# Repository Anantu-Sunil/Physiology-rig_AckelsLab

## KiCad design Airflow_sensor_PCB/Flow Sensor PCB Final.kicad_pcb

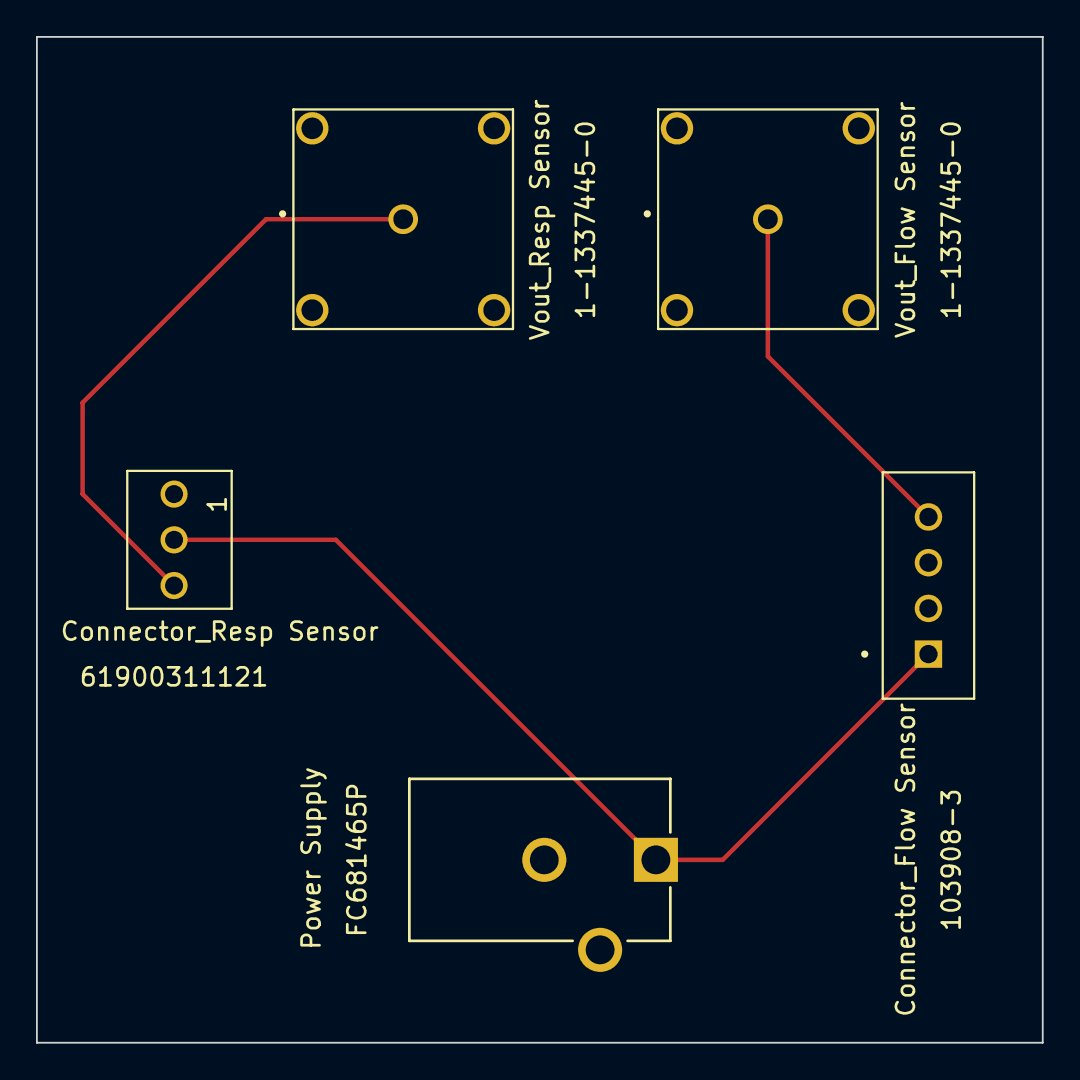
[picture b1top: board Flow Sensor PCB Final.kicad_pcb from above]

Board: 2 copper layers, 55.9 x 55.9 mm, 5 parts (0 on the bottom side), 4 nets.

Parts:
Connector_Flow Sensor: 103908-3; TE_103908-3
Connector_Resp Sensor: 61900311121
Power Supply: FC681465P; CLIFF-FC681465P-0
Vout_Flow Sensor: 1-1337445-0; TE_1-1337445-0
Vout_Resp Sensor: 1-1337445-0; TE_1-1337445-0

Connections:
unnamed: Connector_Flow Sensor.1, Connector_Resp Sensor.2, Power Supply.1
unnamed: Connector_Flow Sensor.2, Connector_Resp Sensor.1, Power Supply.2, Vout_Flow Sensor.2, Vout_Flow Sensor.3, Vout_Flow Sensor.4, Vout_Flow Sensor.5, Vout_Resp Sensor.2, Vout_Resp Sensor.3, Vout_Resp Sensor.4, Vout_Resp Sensor.5
unnamed: Connector_Flow Sensor.4, Vout_Flow Sensor.1
unnamed: Connector_Resp Sensor.3, Vout_Resp Sensor.1

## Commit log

2024-05-10 Start
2024-05-10 PCB folder and bonsai workflow added
2024-05-11 README renamed
2024-07-24 Webcam link updated
2024-09-05 Instructions on pulseBoy installation
2024-09-05 Layout correction
